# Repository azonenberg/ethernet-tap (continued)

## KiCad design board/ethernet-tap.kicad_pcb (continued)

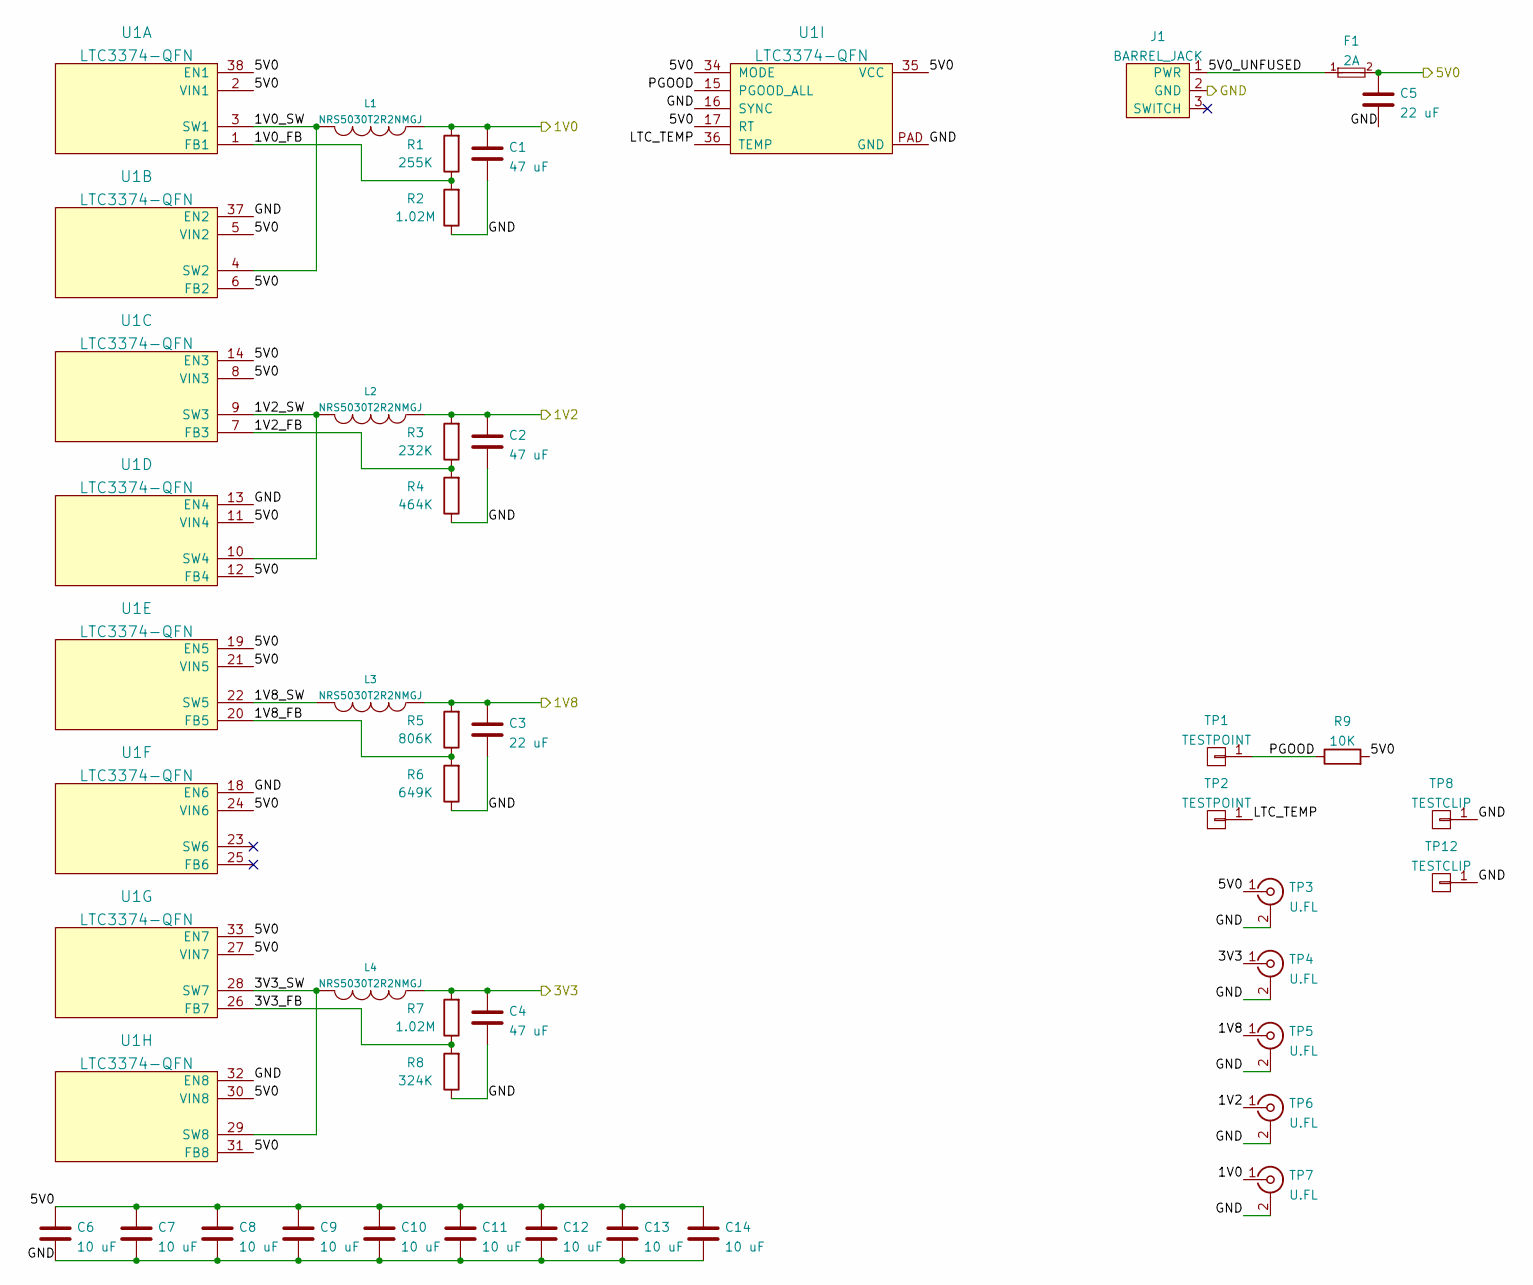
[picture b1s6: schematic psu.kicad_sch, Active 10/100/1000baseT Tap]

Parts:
C1, C2, C4: 47 uF; EIA_1210_CAP_NOSILK
C3, C5: 22 uF; EIA_1206_CAP_NOSILK
C6, C7, C8, C9, C10, C11, C12, C13, C14: 10 uF; EIA_1210_CAP_NOSILK
F1: 2A; EIA_0603_CAP_NOSILK
J1: BARREL_JACK; CONN_CUI_PJ-058BH_HIPWR_BARREL_NOSLOT
L1, L2, L3, L4: NRS5030T2R2NMGJ; INDUCTOR_YUDEN_NRS5030
R1: 255K; EIA_0402_RES_NOSILK
R2, R7: 1.02M; EIA_0402_RES_NOSILK
R3: 232K; EIA_0402_RES_NOSILK
R4: 464K; EIA_0402_RES_NOSILK
R5: 806K; EIA_0402_RES_NOSILK
R6: 649K; EIA_0402_RES_NOSILK
R8: 324K; EIA_0402_RES_NOSILK
R9: 10K; EIA_0402_RES_NOSILK
TP1, TP2: TESTPOINT; TESTPOINT_SMT_0.5MM
TP3, TP4, TP5, TP6, TP7: U.FL; CONN_U.FL_TE_1909763-1
TP8, TP12: TESTCLIP; TESTPOINT_SMT_KEYSTONE_5016
U1: LTC3374-QFN; QFN_38_0.5MM_5x7MM

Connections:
/1V0: C1.1, L1.1, R1.2, TP7.1 (In); also elsewhere on the board
/1V2: C2.1, L2.1, R3.2, TP6.1 (In); also elsewhere on the board
/1V8: C3.1, L3.1, R5.2, TP5.1 (In); also elsewhere on the board
/3V3: C4.1, L4.1, R7.2, TP4.1 (In); also elsewhere on the board
/5V0: C5.1, C6.1, C7.1, C8.1, C9.1, C10.1, C11.1, C12.1, C13.1, C14.1, F1.2, R9.2, TP3.1 (In), U1.2 (VIN1), U1.5 (VIN2), U1.6 (FB2), U1.8 (VIN3), U1.11 (VIN4), U1.12 (FB4), U1.14 (EN3), U1.17 (RT), U1.19 (EN5), U1.21 (VIN5), U1.24 (VIN6), U1.27 (VIN7), U1.30 (VIN8), U1.31 (FB8), U1.33 (EN7), U1.34 (MODE), U1.35 (VCC), U1.38 (EN1); also elsewhere on the board
/GND: C1.2, C2.2, C3.2, C4.2, C5.2, C6.2, C7.2, C8.2, C9.2, C10.2, C11.2, C12.2, C13.2, C14.2, J1.2 (GND), R2.1, R4.1, R6.1, R8.1, TP3.2 (Ext), TP4.2 (Ext), TP5.2 (Ext), TP6.2 (Ext), TP7.2 (Ext), TP8.1, TP12.1, U1.13 (EN4), U1.16 (SYNC), U1.18 (EN6), U1.32 (EN8), U1.37 (EN2), U1.PAD (GND); also elsewhere on the board
/Power Supply/1V0_FB: R1.1, R2.2, U1.1 (FB1)
/Power Supply/1V0_SW: L1.2, U1.3 (SW1), U1.4 (SW2)
/Power Supply/1V2_FB: R3.1, R4.2, U1.7 (FB3)
/Power Supply/1V2_SW: L2.2, U1.9 (SW3), U1.10 (SW4)
/Power Supply/1V8_FB: R5.1, R6.2, U1.20 (FB5)
/Power Supply/1V8_SW: L3.2, U1.22 (SW5)
/Power Supply/3V3_FB: R7.1, R8.2, U1.26 (FB7)
/Power Supply/3V3_SW: L4.2, U1.28 (SW7), U1.29 (SW8)
/Power Supply/5V0_UNFUSED: F1.1, J1.1 (PWR)
/Power Supply/LTC_TEMP: TP2.1, U1.36 (TEMP)
/Power Supply/PGOOD: R9.1, TP1.1, U1.15 (PGOOD_ALL)

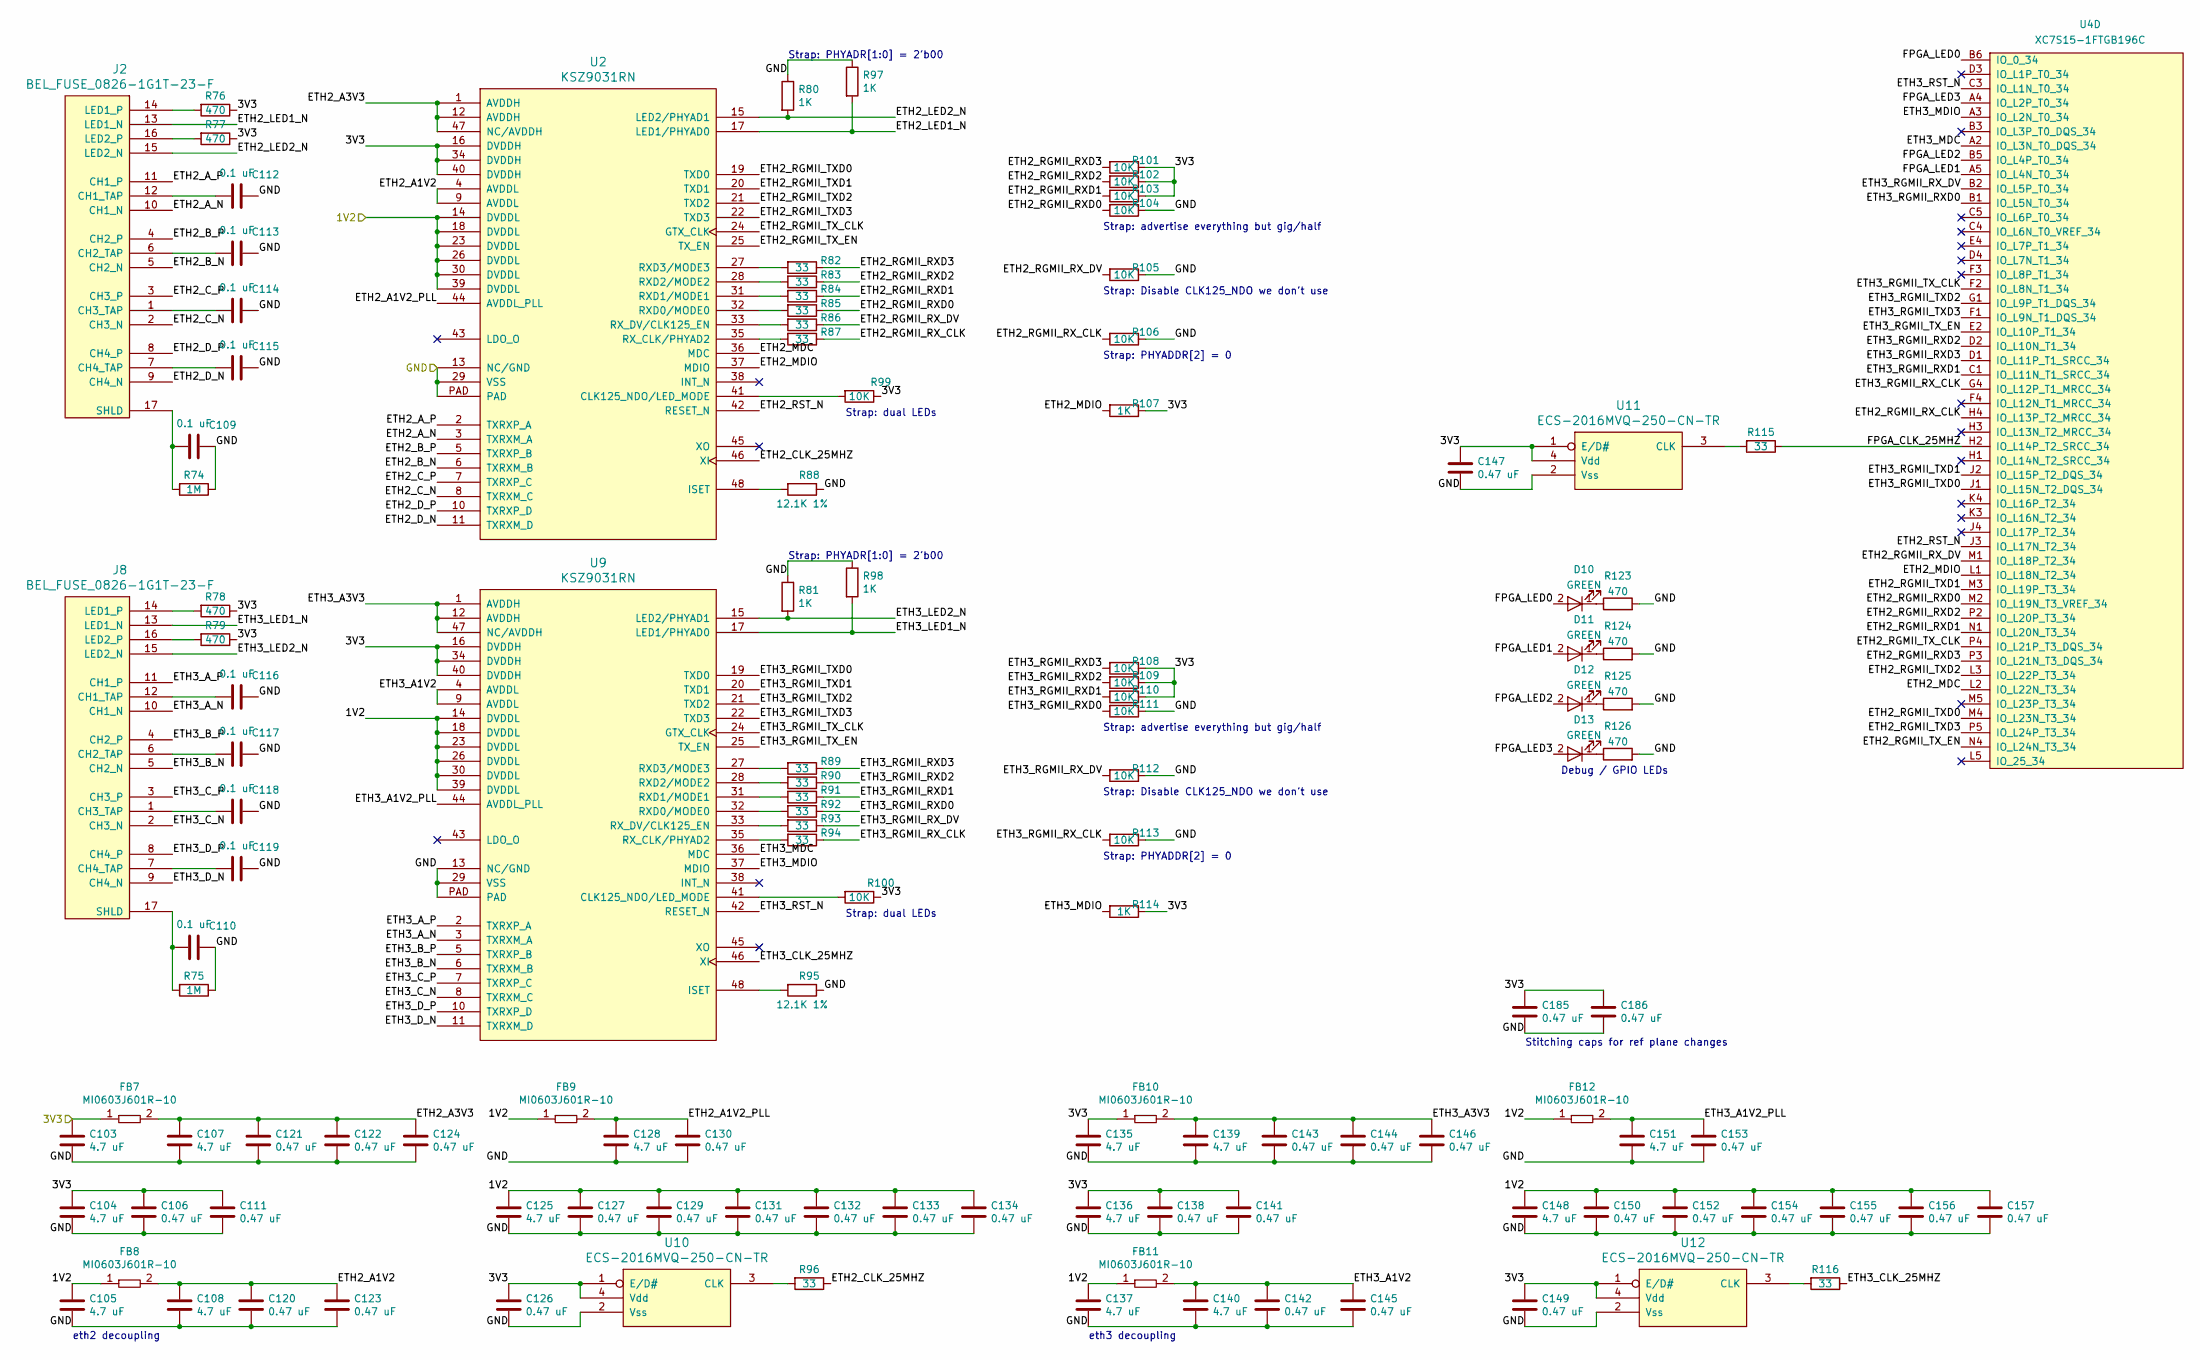
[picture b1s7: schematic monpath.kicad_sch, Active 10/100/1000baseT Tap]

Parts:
C103, C104, C105, C107, C108, C125, C128, C135, C136, C137, C139, C140, C148, C151: 4.7 uF; EIA_0603_CAP_NOSILK
C106, C111, C120, C121, C122, C123, C124, C126, C127, C129, C130, C131, C132, C133, C134, C138, C141, C142, C143, C144, C145, C146, C147, C149, C150, C152, C153, C154, C155, C156, C157, C185, C186: 0.47 uF; EIA_0402_CAP_NOSILK
C109, C110, C112, C113, C114, C115, C116, C117, C118, C119: 0.1 uF; EIA_0402_CAP_NOSILK
D10, D11, D12, D13: GREEN; EIA_0603_LED
FB7, FB8, FB9, FB10, FB11, FB12: MI0603J601R-10; EIA_0603_INDUCTOR_NOSILK
J2, J8: BEL_FUSE_0826-1G1T-23-F; CONN_BELFUSE_0826_1G1T_23_F
R74, R75: 1M; EIA_0402_RES_NOSILK
R76, R77, R78, R79, R123, R124, R125, R126: 470; EIA_0402_RES_NOSILK
R80, R81, R97, R98, R107, R114: 1K; EIA_0402_RES_NOSILK
R82, R83, R84, R85, R86, R87, R89, R90, R91, R92, R93, R94, R96, R115, R116: 33; EIA_0402_RES_NOSILK
R88, R95: 12.1K 1%; EIA_0402_RES_NOSILK
R99, R100, R101, R102, R103, R104, R105, R106, R108, R109, R110, R111, R112, R113: 10K; EIA_0402_RES_NOSILK
U2, U9: KSZ9031RN; QFN_48_0.5MM_7x7MM
U4: XC7S15-1FTGB196C; BGA_196_15x15_FULLARRAY_1MM_FTGB196
U10, U11, U12: ECS-2016MVQ-250-CN-TR; OSCILLATOR_2.0x1.6

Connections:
/1V2: C105.1, C125.1, C127.1, C129.1, C131.1, C132.1, C133.1, C134.1, C137.1, C148.1, C150.1, C152.1, C154.1, C155.1, C156.1, C157.1, FB8.1, FB9.1, FB11.1, FB12.1, U2.14 (DVDDL), U2.18 (DVDDL), U2.23 (DVDDL), U2.26 (DVDDL), U2.30 (DVDDL), U2.39 (DVDDL), U9.14 (DVDDL), U9.18 (DVDDL), U9.23 (DVDDL), U9.26 (DVDDL), U9.30 (DVDDL), U9.39 (DVDDL); also elsewhere on the board
/3V3: C103.1, C104.1, C106.1, C111.1, C126.1, C135.1, C136.1, C138.1, C141.1, C147.1, C149.1, C185.1, C186.1, FB7.1, FB10.1, R76.1, R77.1, R78.1, R79.1, R99.1, R100.1, R101.1, R102.1, R103.1, R107.1, R108.1, R109.1, R110.1, R114.1, U2.16 (DVDDH), U2.34 (DVDDH), U2.40 (DVDDH), U9.16 (DVDDH), U9.34 (DVDDH), U9.40 (DVDDH), U10.1 (E/D#), U10.4 (Vdd), U11.1 (E/D#), U11.4 (Vdd), U12.1 (E/D#), U12.4 (Vdd); also elsewhere on the board
/GND: C103.2, C104.2, C105.2, C106.2, C107.2, C108.2, C109.1, C110.1, C111.2, C112.1, C113.1, C114.1, C115.1, C116.1, C117.1, C118.1, C119.1, C120.2, C121.2, C122.2, C123.2, C124.2, C125.2, C126.2, C127.2, C128.2, C129.2, C130.2, C131.2, C132.2, C133.2, C134.2, C135.2, C136.2, C137.2, C138.2, C139.2, C140.2, C141.2, C142.2, C143.2, C144.2, C145.2, C146.2, C147.2, C148.2, C149.2, C150.2, C151.2, C152.2, C153.2, C154.2, C155.2, C156.2, C157.2, C185.2, C186.2, R74.1, R75.1, R80.1, R81.1, R88.1, R95.1, R97.1, R98.1, R104.1, R105.1, R106.1, R111.1, R112.1, R113.1, R123.2, R124.2, R125.2, R126.2, U2.13 (NC/GND), U2.29 (VSS), U2.PAD, U9.13 (NC/GND), U9.29 (VSS), U9.PAD, U10.2 (Vss), U11.2 (Vss), U12.2 (Vss); also elsewhere on the board
/Monitor Path/ETH2_A1V2: C108.1, C120.1, C123.1, FB8.2, U2.4 (AVDDL), U2.9 (AVDDL)
/Monitor Path/ETH2_A1V2_PLL: C128.1, C130.1, FB9.2, U2.44 (AVDDL_PLL)
/Monitor Path/ETH2_A3V3: C107.1, C121.1, C122.1, C124.1, FB7.2, U2.1 (AVDDH), U2.12 (AVDDH), U2.47 (NC/AVDDH)
/Monitor Path/ETH2_A_N: J2.10 (CH1_N), U2.3 (TXRXM_A)
/Monitor Path/ETH2_A_P: J2.11 (CH1_P), U2.2 (TXRXP_A)
/Monitor Path/ETH2_B_N: J2.5 (CH2_N), U2.6 (TXRXM_B)
/Monitor Path/ETH2_B_P: J2.4 (CH2_P), U2.5 (TXRXP_B)
/Monitor Path/ETH2_CLK_25MHZ: R96.1, U2.46 (XI)
/Monitor Path/ETH2_C_N: J2.2 (CH3_N), U2.8 (TXRXM_C)
/Monitor Path/ETH2_C_P: J2.3 (CH3_P), U2.7 (TXRXP_C)
/Monitor Path/ETH2_D_N: J2.9 (CH4_N), U2.11 (TXRXM_D)
/Monitor Path/ETH2_D_P: J2.8 (CH4_P), U2.10 (TXRXP_D)
/Monitor Path/ETH2_LED1_N: J2.13 (LED1_N), R97.2, U2.17 (LED1/PHYAD0)
/Monitor Path/ETH2_LED2_N: J2.15 (LED2_N), R80.2, U2.15 (LED2/PHYAD1)
/Monitor Path/ETH2_MDC: U2.36 (MDC), U4.L2 (IO_L22N_T3_34)
/Monitor Path/ETH2_MDIO: R107.2, U2.37 (MDIO), U4.L1 (IO_L18N_T2_34)
/Monitor Path/ETH2_RGMII_RXD0: R85.1, R104.2, U4.M2 (IO_L19N_T3_VREF_34)
/Monitor Path/ETH2_RGMII_RXD1: R84.1, R103.2, U4.N1 (IO_L20N_T3_34)
/Monitor Path/ETH2_RGMII_RXD2: R83.1, R102.2, U4.P2 (IO_L20P_T3_34)
/Monitor Path/ETH2_RGMII_RXD3: R82.1, R101.2, U4.P3 (IO_L21N_T3_DQS_34)
/Monitor Path/ETH2_RGMII_RX_CLK: R87.1, R106.2, U4.H4 (IO_L13P_T2_MRCC_34)
/Monitor Path/ETH2_RGMII_RX_DV: R86.1, R105.2, U4.M1 (IO_L18P_T2_34)
/Monitor Path/ETH2_RGMII_TXD0: U2.19 (TXD0), U4.M4 (IO_L23N_T3_34)
/Monitor Path/ETH2_RGMII_TXD1: U2.20 (TXD1), U4.M3 (IO_L19P_T3_34)
/Monitor Path/ETH2_RGMII_TXD2: U2.21 (TXD2), U4.L3 (IO_L22P_T3_34)
/Monitor Path/ETH2_RGMII_TXD3: U2.22 (TXD3), U4.P5 (IO_L24P_T3_34)
/Monitor Path/ETH2_RGMII_TX_CLK: U2.24 (GTX_CLK), U4.P4 (IO_L21P_T3_DQS_34)
/Monitor Path/ETH2_RGMII_TX_EN: U2.25 (TX_EN), U4.N4 (IO_L24N_T3_34)
/Monitor Path/ETH2_RST_N: U2.42 (RESET_N), U4.J3 (IO_L17N_T2_34)
/Monitor Path/ETH3_A1V2: C140.1, C142.1, C145.1, FB11.2, U9.4 (AVDDL), U9.9 (AVDDL)
/Monitor Path/ETH3_A1V2_PLL: C151.1, C153.1, FB12.2, U9.44 (AVDDL_PLL)
/Monitor Path/ETH3_A3V3: C139.1, C143.1, C144.1, C146.1, FB10.2, U9.1 (AVDDH), U9.12 (AVDDH), U9.47 (NC/AVDDH)
/Monitor Path/ETH3_A_N: J8.10 (CH1_N), U9.3 (TXRXM_A)
/Monitor Path/ETH3_A_P: J8.11 (CH1_P), U9.2 (TXRXP_A)
/Monitor Path/ETH3_B_N: J8.5 (CH2_N), U9.6 (TXRXM_B)
/Monitor Path/ETH3_B_P: J8.4 (CH2_P), U9.5 (TXRXP_B)
/Monitor Path/ETH3_CLK_25MHZ: R116.1, U9.46 (XI)
/Monitor Path/ETH3_C_N: J8.2 (CH3_N), U9.8 (TXRXM_C)
/Monitor Path/ETH3_C_P: J8.3 (CH3_P), U9.7 (TXRXP_C)
/Monitor Path/ETH3_D_N: J8.9 (CH4_N), U9.11 (TXRXM_D)
/Monitor Path/ETH3_D_P: J8.8 (CH4_P), U9.10 (TXRXP_D)
/Monitor Path/ETH3_LED1_N: J8.13 (LED1_N), R98.2, U9.17 (LED1/PHYAD0)
/Monitor Path/ETH3_LED2_N: J8.15 (LED2_N), R81.2, U9.15 (LED2/PHYAD1)
/Monitor Path/ETH3_MDC: U4.A2 (IO_L3N_T0_DQS_34), U9.36 (MDC)
/Monitor Path/ETH3_MDIO: R114.2, U4.A3 (IO_L2N_T0_34), U9.37 (MDIO)
/Monitor Path/ETH3_RGMII_RXD0: R92.1, R111.2, U4.B1 (IO_L5N_T0_34)
/Monitor Path/ETH3_RGMII_RXD1: R91.1, R110.2, U4.C1 (IO_L11N_T1_SRCC_34)
/Monitor Path/ETH3_RGMII_RXD2: R90.1, R109.2, U4.D2 (IO_L10N_T1_34)
/Monitor Path/ETH3_RGMII_RXD3: R89.1, R108.2, U4.D1 (IO_L11P_T1_SRCC_34)
/Monitor Path/ETH3_RGMII_RX_CLK: R94.1, R113.2, U4.G4 (IO_L12P_T1_MRCC_34)
/Monitor Path/ETH3_RGMII_RX_DV: R93.1, R112.2, U4.B2 (IO_L5P_T0_34)
/Monitor Path/ETH3_RGMII_TXD0: U4.J1 (IO_L15N_T2_DQS_34), U9.19 (TXD0)
/Monitor Path/ETH3_RGMII_TXD1: U4.J2 (IO_L15P_T2_DQS_34), U9.20 (TXD1)
/Monitor Path/ETH3_RGMII_TXD2: U4.G1 (IO_L9P_T1_DQS_34), U9.21 (TXD2)
/Monitor Path/ETH3_RGMII_TXD3: U4.F1 (IO_L9N_T1_DQS_34), U9.22 (TXD3)
/Monitor Path/ETH3_RGMII_TX_CLK: U4.F2 (IO_L8N_T1_34), U9.24 (GTX_CLK)
/Monitor Path/ETH3_RGMII_TX_EN: U4.E2 (IO_L10P_T1_34), U9.25 (TX_EN)
/Monitor Path/ETH3_RST_N: U4.C3 (IO_L1N_T0_34), U9.42 (RESET_N)
/Monitor Path/FPGA_CLK_25MHZ: R115.1, U4.H2 (IO_L14P_T2_SRCC_34)
/Monitor Path/FPGA_LED0: D10.2 (A), U4.B6 (IO_0_34)
/Monitor Path/FPGA_LED1: D11.2 (A), U4.A5 (IO_L4N_T0_34)
/Monitor Path/FPGA_LED2: D12.2 (A), U4.B5 (IO_L4P_T0_34)
/Monitor Path/FPGA_LED3: D13.2 (A), U4.A4 (IO_L2P_T0_34)
unnamed: C109.2, J2.17 (SHLD), R74.2
unnamed: C110.2, J8.17 (SHLD), R75.2
unnamed: C112.2, J2.12 (CH1_TAP)
unnamed: C113.2, J2.6 (CH2_TAP)
unnamed: C114.2, J2.1 (CH3_TAP)
unnamed: C115.2, J2.7 (CH4_TAP)
unnamed: C116.2, J8.12 (CH1_TAP)
unnamed: C117.2, J8.6 (CH2_TAP)
unnamed: C118.2, J8.1 (CH3_TAP)
unnamed: C119.2, J8.7 (CH4_TAP)
unnamed: D10.1 (K), R123.1
unnamed: D11.1 (K), R124.1
unnamed: D12.1 (K), R125.1
unnamed: D13.1 (K), R126.1
unnamed: J2.14 (LED1_P), R76.2
unnamed: J2.16 (LED2_P), R77.2
unnamed: J8.14 (LED1_P), R78.2
unnamed: J8.16 (LED2_P), R79.2
unnamed: R82.2, U2.27 (RXD3/MODE3)
unnamed: R83.2, U2.28 (RXD2/MODE2)
unnamed: R84.2, U2.31 (RXD1/MODE1)
unnamed: R85.2, U2.32 (RXD0/MODE0)
unnamed: R86.2, U2.33 (RX_DV/CLK125_EN)
unnamed: R87.2, U2.35 (RX_CLK/PHYAD2)
unnamed: R88.2, U2.48 (ISET)
unnamed: R89.2, U9.27 (RXD3/MODE3)
unnamed: R90.2, U9.28 (RXD2/MODE2)
unnamed: R91.2, U9.31 (RXD1/MODE1)
unnamed: R92.2, U9.32 (RXD0/MODE0)
unnamed: R93.2, U9.33 (RX_DV/CLK125_EN)
unnamed: R94.2, U9.35 (RX_CLK/PHYAD2)
unnamed: R95.2, U9.48 (ISET)
unnamed: R96.2, U10.3 (CLK)
unnamed: R99.2, U2.41 (CLK125_NDO/LED_MODE)
unnamed: R100.2, U9.41 (CLK125_NDO/LED_MODE)
unnamed: R115.2, U11.3 (CLK)
unnamed: R116.2, U12.3 (CLK)

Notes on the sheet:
Strap: dual LEDs
Strap: PHYADR[1:0] = 2'b00
eth2 decoupling
Strap: PHYADDR[2] = 0
Strap: Disable CLK125_NDO we don't use
Strap: advertise everything but gig/half
eth3 decoupling
Stitching caps for ref plane changes
Debug / GPIO LEDs

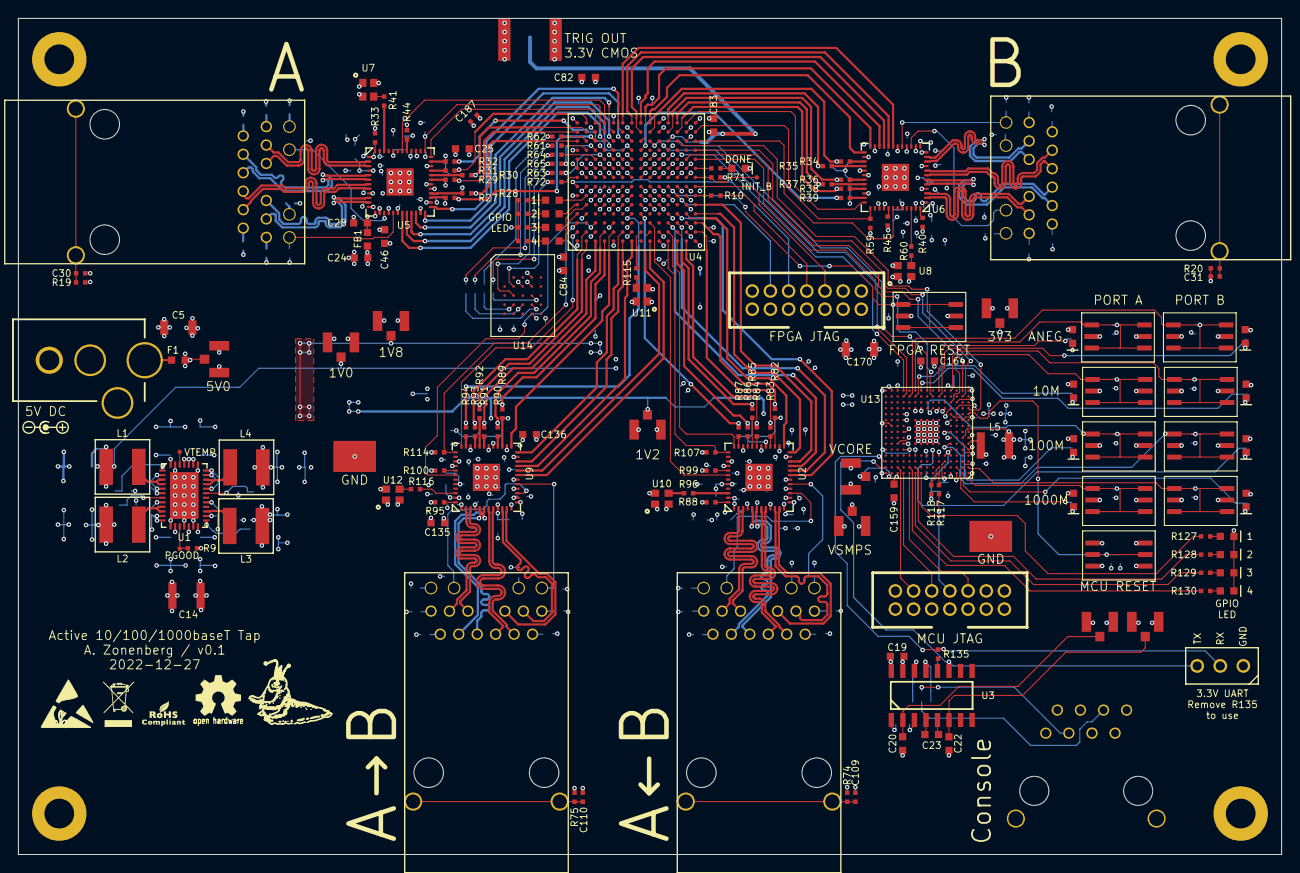
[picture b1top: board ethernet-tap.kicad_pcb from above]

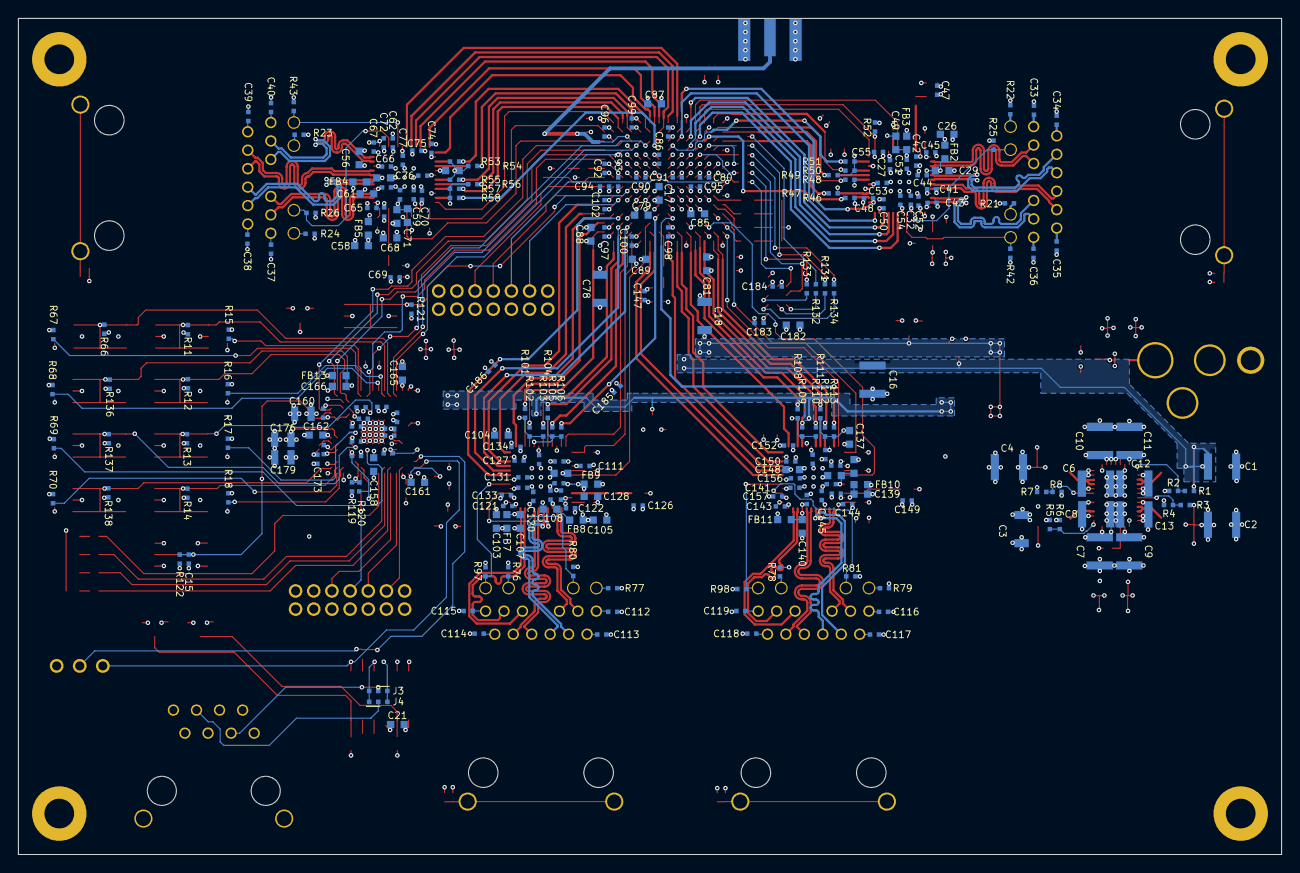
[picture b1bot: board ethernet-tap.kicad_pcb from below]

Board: 4 copper layers, 139.0 x 92.0 mm, 415 parts (252 on the bottom side), 297 nets.

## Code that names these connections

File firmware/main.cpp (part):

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{
	//Initialize the UART for local console: 115.2 Kbps using PA12 for UART4 transmit and PA11 for UART2 receive
	//TODO: nice interface for enabling UART interrupts
	GPIOPin uart_tx(&GPIOA, 12, GPIOPin::MODE_PERIPHERAL, GPIOPin::SLEW_SLOW, 6);
	GPIOPin uart_rx(&GPIOA, 11, GPIOPin::MODE_PERIPHERAL, GPIOPin::SLEW_SLOW, 6);

	//Default after reset is for UART4 to be clocked by PCLK1 (APB1 clock) which is 64 MHz
	//So we need a divisor of 556
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void UpdateSpeedLEDs()
{
	//LEDs
	static GPIOPin left_aneg_en(&GPIOC, 4, GPIOPin::MODE_OUTPUT, GPIOPin::SLEW_SLOW);
	static GPIOPin left_10m_en(&GPIOB, 11, GPIOPin::MODE_OUTPUT, GPIOPin::SLEW_SLOW);
	static GPIOPin left_100m_en(&GPIOF, 3, GPIOPin::MODE_OUTPUT, GPIOPin::SLEW_SLOW);
	static GPIOPin left_1000m_en(&GPIOB, 9, GPIOPin::MODE_OUTPUT, GPIOPin::SLEW_SLOW);

	static GPIOPin right_aneg_en(&GPIOA, 5, GPIOPin::MODE_OUTPUT, GPIOPin::SLEW_SLOW);
	static GPIOPin right_10m_en(&GPIOE, 10, GPIOPin::MODE_OUTPUT, GPIOPin::SLEW_SLOW);
	static GPIOPin right_100m_en(&GPIOG, 15, GPIOPin::MODE_OUTPUT, GPIOPin::SLEW_SLOW);
	static GPIOPin right_1000m_en(&GPIOB, 8, GPIOPin::MODE_OUTPUT, GPIOPin::SLEW_SLOW);

	//Get advertised speeds/modes for each port
	auto leftAd = PhyRegisterRead(0, PHY_REG_AN_ADVERT);
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{
	static bool changedLastTime = false;

	static GPIOPin left_aneg_sw(&GPIOF, 14, GPIOPin::MODE_INPUT, GPIOPin::SLEW_SLOW);
	static GPIOPin left_10m_sw(&GPIOH, 2, GPIOPin::MODE_INPUT, GPIOPin::SLEW_SLOW);
	static GPIOPin left_100m_sw(&GPIOC, 5, GPIOPin::MODE_INPUT, GPIOPin::SLEW_SLOW);
	static GPIOPin left_1000m_sw(&GPIOE, 3, GPIOPin::MODE_INPUT, GPIOPin::SLEW_SLOW);

	static GPIOPin right_aneg_sw(&GPIOF, 12, GPIOPin::MODE_INPUT, GPIOPin::SLEW_SLOW);
	static GPIOPin right_10m_sw(&GPIOH, 3, GPIOPin::MODE_INPUT, GPIOPin::SLEW_SLOW);
	static GPIOPin right_100m_sw(&GPIOF, 0, GPIOPin::MODE_INPUT, GPIOPin::SLEW_SLOW);
	static GPIOPin right_1000m_sw(&GPIOE, 4, GPIOPin::MODE_INPUT, GPIOPin::SLEW_SLOW);

	//Read switches
	bool left_aneg = left_aneg_sw;
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
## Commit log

2022-12-20 Added ipcores submodule
2022-12-20 Added license header
2022-12-20 Initial power budget docs
2022-12-20 Initial schematic
2022-12-20 Continued initial schematic capture
2022-12-21 Finished initial schematic, ready for signoff review
2022-12-21 Finished schematic review. Added a few more test points.
2022-12-21 Continued initial layout. First PHY fully routed including connection to FPGA. Hooked up 0402 bypass caps under FPGA. Flash is roughly placed.
2022-12-21 Good progress hooking up second PHY
2022-12-22 Continued initial layout. Good progress on monitor port PHYs.
2022-12-23 Continued work on monitor port PHY layout
2022-12-23 Shrunk board down to 139 x 92 mm
2022-12-23 Finished power supply layout, added mounting holes and a bunch of silkscreen labeling
2022-12-24 Continued work on layout. Monitor port PHys are now done, as is FPGA JTAG and reset
2022-12-24 Good progress on initial layout of MCU subsystem
2022-12-26 Updating file: ethernet-tap.kicad_pcb with current fully routed design.
2022-12-27 Finished power plane routing, moved some signals around to reduce layer split crossings
2022-12-27 DRC fixes to layout
2022-12-27 Final v0.1 layout after design review
2023-01-18 Updated submodules
2023-01-18 Initial Vivado project
2023-01-18 Initial OpenOCD configuration
2023-01-18 Initial test firmware with minimal CLI etc
2023-01-18 FPGA and MCU are now talking via quad SPI
2023-01-18 Added MDIO register read support
2023-01-18 Implemented initial PHY register read/write including indirect
2023-01-18 Added link speed reporting
2023-01-18 Implemented "show int status" command
2023-01-19 Initial firmware is now at minimum viable "no-frills tap" stage
2023-01-19 Tweaks to drive strength for SI
2023-01-19 Config fixes for quad SPI mode. Fixed swapped MDIO/MDC on monA/monB interfaces. Added boot time delay to make sure FPGA is ready before we start trying to poke registers.
2023-01-19 Added CLI commands to read registers
2023-01-19 Added commands to write (non MMD) phy registers
2023-01-19 Packet datapath now resets when link speed or state changes
2023-01-20 Implemented "no speed" command
2023-01-20 Implemented TDR cable test
2023-01-21 Initial support to disable AN and force specific speeds
2023-01-21 Added raw MMD register write command
2023-01-21 Added "show volatility"
2023-01-21 Minor grammar fixes to "show volatility"
2023-01-21 Added "show detail" interface command to print almost all PHY registers
2023-01-21 Added test pattern support
2023-01-21 Added 1000base-T master-slave mode override
2023-01-21 Added MDI / MDI-X override
2023-01-22 Added trigger output
2023-01-22 Updated antikernel-ipcores with fix for hang on >=1024 byte packets
